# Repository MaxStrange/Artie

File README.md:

# Artie

**This code is pre-release: you cannot yet build an Artie bot nor can you use the framework - not all of the software and hardware is ready!**

Artie is an open source developmental robotics platform. This repository is the
documentation hub and the place to start; the software itself lives in the component
repositories listed below.

The purpose of Artie is twofold: data collection and testing developmental robotics theories.

The vision is that Artie will be fully open source, 3D-printable, and as cheap as is feasible,
while still being easy to use and extend.

Fundamentally, this project provides:

* A software development kit (ArDK) - code libraries for use building robots
* A platform - a suite of tools and documents for building a Kubernetes cluster designed from the ground-up
  for research
* A reference robot (Artie00) - if you want to build your own completely different robot from the one we
  use, that's fine! But you might want to use Artie00 as a reference

## The repositories

| Repository | What it is |
|---|---|
| **Artie** (this one) | Documentation, architecture, getting started. Cite this repository. |
| [ArDK](https://github.com/ArtieBots/ArDK) | The Artie Development Kit: the libraries you write applications and drivers against, the platform services, the base Docker image, and the protocol specifications. |
| [ArtieTool](https://github.com/ArtieBots/ArtieTool) | Builds, tests, flashes and deploys everything. Installs the `artie-tool` command. |
| [ArtieWorkbench](https://github.com/ArtieBots/ArtieWorkbench) | The graphical application most people use to set up and drive an Artie Framework robot. |
| [ArtieCLI](https://github.com/ArtieBots/ArtieCLI) | A command line interface to a running robot, for testing and low-level debugging. |
| [ArtieDaemons](https://github.com/ArtieBots/ArtieDaemons) | Host daemons for the Kubernetes cluster an Artie robot runs on. |
| [Artie00](https://github.com/ArtieBots/Artie00) | The first Artie: its hardware manifest, bill of materials, firmware, drivers and schematics. |

Your own code stays in your own repository. You depend on Artie's libraries, build your
applications and firmware into images following the usage guidelines, and deploy them
with Helm - normally through Artie Workbench or Artie Tool.

## Get Started

**Looking for the contributing guide?** [See here](./CONTRIBUTING.md)

### Using Artie

Most people will want Artie Workbench, which installs Artie Tool along with it. This is
a graphical application that should make using an Artie Framework robot easy (for a human):

```bash
pip install artieworkbench
artie-workbench
```

If you would rather work from a terminal, or you are automating something:

```bash
pip install artietool
artie-tool workspace status    # where each component resolves to
artie-tool workspace sync      # clone the components you want to build from source
artie-tool build all           # by default, builds the latest stable framework components
artie-tool deploy artie        # will only work if you have something to deploy to
```

Artie Tool reads its configuration from `~/.artie/config.yaml`, from `ARTIE_*` environment
variables, and from command line arguments, in increasing order of precedence. Point a
component at a checkout of your own and Artie Tool will build from it instead:

```yaml
# ~/.artie/config.yaml
workspace: ~/artie-workspace
repos:
  ardk: { path: ~/repos/ArDK }   # your working copy; sync leaves it alone; build will pick it up
```

Which versions of the components are tested against a real robot and therefore form a known stable
release is stated by a release manifest -
see [versioning and releases](./docs/contributing/versioning.md).
*That manifest is what to attach to an experiment's data and cite in a paper.*

### Building Artie00

Before you can use Artie, you need to build him.

**Please note:** you cannot yet build an Artie! These instructions will certainly change, the bill of materials
will change, the schematics will change, etc.

Building Artie is composed of the following steps:

1. Get your parts
1. Flash the parts
1. Build your bot

[See here for the full instructions](./docs/building/building-artie-main.md)

### Building a Custom Robot

Artie Framework doesn't just work with official Artie robots! Artie Framework provides tools for managing
an awful lot of complexity behind convenient tooling while bringing you things like:

* Data provenance
* Reliability
* Repeatability

- the types of things that are super important in scientific endeavors.

[See here for how to bring your own robot](./docs/building/bring-your-own.md)

### Artie Out of the Box

Once you have built an Artie (or brought your own robot),
[see here for instructions on using your Artie](./docs/out-of-the-box/getting-started.md).

## Motivation

### Why Developmental Robotics?

Developmental robotics is the study of human development by means of simulating it.
It is an important field of study for at least the following reasons:

1. Developmental robotics informs the study of human development. What better way to test a theory
   of how a human develops than to try to build a human?
1. Developmental robotics informs the study of artificial intelligence. AI can benefit from any advances
   in our understanding of human intelligence.
1. Developmental robotics informs the study of robotics. Building a robot always involves solving difficult
   engineering problems. Building a robot that can learn and adapt like a human is even more difficult,
   and any advances in this field will likely have applications in more traditional robotics or in soft robotics.

Here's a great excerpt from Wikipedia:

> As in human children, learning is expected to be cumulative and of progressively increasing complexity,
  and to result from self-exploration of the world in combination with social interaction.
  The typical methodological approach consists in starting from theories of human and animal development
  elaborated in fields such as developmental psychology, neuroscience, developmental and evolutionary biology,
  and linguistics, then to formalize and implement them in robots

### Embodiment

A central tenet of developmental robotics is that embodiment (agency) is necessary for intelligence.
Human intelligence stems from a need to manipulate the world and ourselves in response to the world.
It does not exist in a vacuum. Hence, it makes sense to embody an intelligent agent in a physical
(or at least virtual) world.

### Why a Robot?

If developmental robotics is the study of human development by means of simulating it, why
build an actual robot? Why not just simulate one in a physics simulator?

The answer is simple: humans aren't simulated - they exist in a messy, physical world. Any theory
of how a human develops must ultimately be put to the test in the same world with the same parameters.
In fact, when you try to go from a theory to a physical implementation, you always find that the theory
was underspecified: in implementing the theory, you have to make decisions about things that the theory
did not address. This process of implementation forces you to refine the theory and address gaps that
you did not know existed.

Nonetheless, there is a place for virtual simulation in developmental robotics, and Artie
will hopefully incorporate a simulator, since working with an actual robot is way less convenient
than working in a video game, but this simulator is a long way off for now. Get in touch if
you'd like to help build it!

One last thing about robots: embodiment is a two-way street. Though you can get by to an extent with
datasets that are impersonal and aggregated (as in the typical supervised learning paradigm of machine learning),
humans do not learn this way. Humans learn from interacting with their environment and by their environment
interacting with them. Parents speak directly to their children using infant-directed speech, based on
what their children are currently doing. Teenagers navigate social environments that are unique to their
particular group of friends. Young adults take elective classes at university that are interesting to them.
*An intelligent agent has an active, often causative relationship with the data from which it learns.*
Hence, you need to place the subject into an environment to truly study the development of natural intelligence.

Finally, robots are awesome!

### Why not Buy a Robot that Already Exists?

We found that we needed a robot that fulfilled the following criteria:

* Open Source - both hardware and software
* Affordable - we wanted to be able to build multiple copies of the robot without grant funding.
  We think this is key: robotics research is slowly coming to the masses of hobbyists, students,
  and citizen scientists, but developmental robotics research is still mostly confined to well-funded labs.
* Designed for Developmental Robotics - many existing robots are designed for other purposes,
  such as research in traditional robotics, human-robot interaction, or AI. These robots never
  take into account the specific needs of developmental robotics research, such as the physical constraints
  of a human infant, or the physiological requirements of various sensor components. Artie is designed
  from the ground up with developmental robotics in mind: we have compromised on biomimeticity only as far
  as is absolutely necessary to make the robot affordable and buildable.
* Modular and Extensible - we wanted a robot that could be easily modified, extended, and repaired.
  Research moves quickly, and we wanted a robot that could keep pace.
  We also wanted a robot that could be customized to fit the needs of different researchers
  and different experiments, which means that we aren't building a robot - we are building a robotics ecosystem.
* Professional grade - we wanted a robot that was reliable and fun to use. Every layer of Artie's
  software stack is designed to be robust, maintainable, and to follow engineering best practices,
  so that researchers can focus on their research, not on debugging the robot.
* Data provenance and reproducibility - we wanted a robot that could keep track of where its data came from, so that
  researchers can be sure that their experiments are reproducible and that their data is trustworthy.
  Artie uses containerization and orchestration to ensure that software environments are consistent
  across different deployments. Additionally, even the single board computers are running custom
  Linux images built using Yocto, so that the entire software stack is under control: if it worked once,
  it should work every time; you are running an experiment with Artie, not just getting him to work this one time.

Alternatives exist, but they don't meet these criteria. For example, there's:
  - [Poppy](https://www.generationrobots.com/en/312-poppy-humanoid-robot), which is about $10k USD,
    and while it's open source and extensible, it's not designed specifically for developmental robotics; it is
    not biomimetic at all.
  - [Nao](https://en.wikipedia.org/wiki/Nao_(robot)), which is about $15k USD, and while it is well-regarded
    and used extensively, its hardware is not extensible or modifiable, and it
    is designed more for human-robot interaction than developmental robotics. Again, very little biomimeticity.
  - [iCub](https://icub.iit.it/products/product-catalog), which is about $250k USD, and while it is
    designed for developmental robotics and has a high degree of biomimeticity, its cost
    makes it inaccessible to most researchers - particularly to citizen scientists or students.
  - [Berkeley Humanoid Lite](https://lite.berkeley-humanoid.org/), which is about $5k USD, and while it is affordable
    and open source, it is not designed specifically for developmental robotics, again with very little biomimeticity
    in mind.

### Why not ROS?

Additionally, we did not use ROS (Robot Operating System) as the basis for Artie's software stack.
While ROS is a great tool for traditional robotics development, we felt it was not well-suited
for reproducible developmental robotics research. ROS's architecture is not designed
for containerization and orchestration, which are key to ensuring that experiments
are reproducible and that software environments are consistent across different deployments.
Also, while ROS has a huge ecosystem and excellent community support/adoption, it is too general purpose
for our needs: we wanted a software stack that was specifically designed for developmental robotics and for research.
Really the only thing that we could have used from ROS was its inter-process communication (IPC) mechanisms.
I suppose its physics simulator would have been nice, too.

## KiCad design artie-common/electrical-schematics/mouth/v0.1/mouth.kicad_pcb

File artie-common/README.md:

# Artie Common

This folder contains a bunch of common components used between different versions of Artie,
but which do not belong in the framework (i.e., they do not necessarily belong to *all*
versions of Artie, but they are used by more than one).

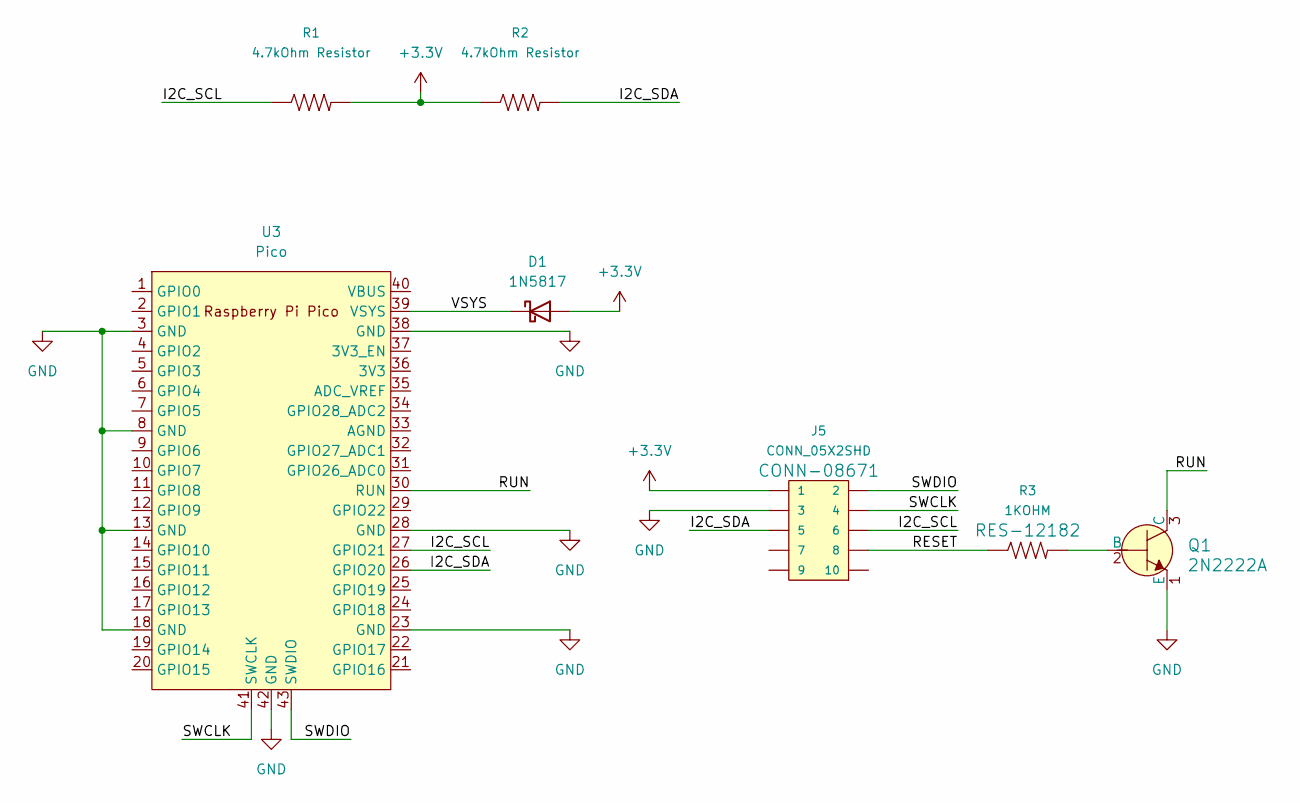
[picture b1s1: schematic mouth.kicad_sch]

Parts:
D1: 1N5817; D_DO-41_SOD81_P10.16mm_Horizontal
J5: CONN_05X2SHD; 2X5-SHROUDED
Q1: 2N2222A; TO-18-3; MPN 2N2222A; Digi-Key_PN 2N2222ACS-ND
R1, R2: 4.7kOhm Resistor; AXIAL-0.3
R3: 1KOHM; AXIAL-0.3-KIT
U3: Pico; RPi_Pico_SMD_TH

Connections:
+3.3V: D1.2 (A), J5.1, R1.P$2 (2), R2.P$1 (1)
/I2C_SCL: J5.6, R1.P$1 (1), U3.27 (GPIO21)
/I2C_SDA: J5.5, R2.P$2 (2), U3.26 (GPIO20)
/RESET: J5.8, R3.P$1 (1)
/RUN: Q1.3 (C), U3.30 (RUN)
/SWCLK: J5.4, U3.41 (SWCLK)
/SWDIO: J5.2, U3.43 (SWDIO)
/VSYS: D1.1 (K), U3.39 (VSYS)
GND: J5.3, Q1.1 (E), U3.3 (GND), U3.8 (GND), U3.13 (GND), U3.18 (GND), U3.23 (GND), U3.28 (GND), U3.38 (GND), U3.42 (GND)
unnamed: Q1.2 (B), R3.P$2 (2)

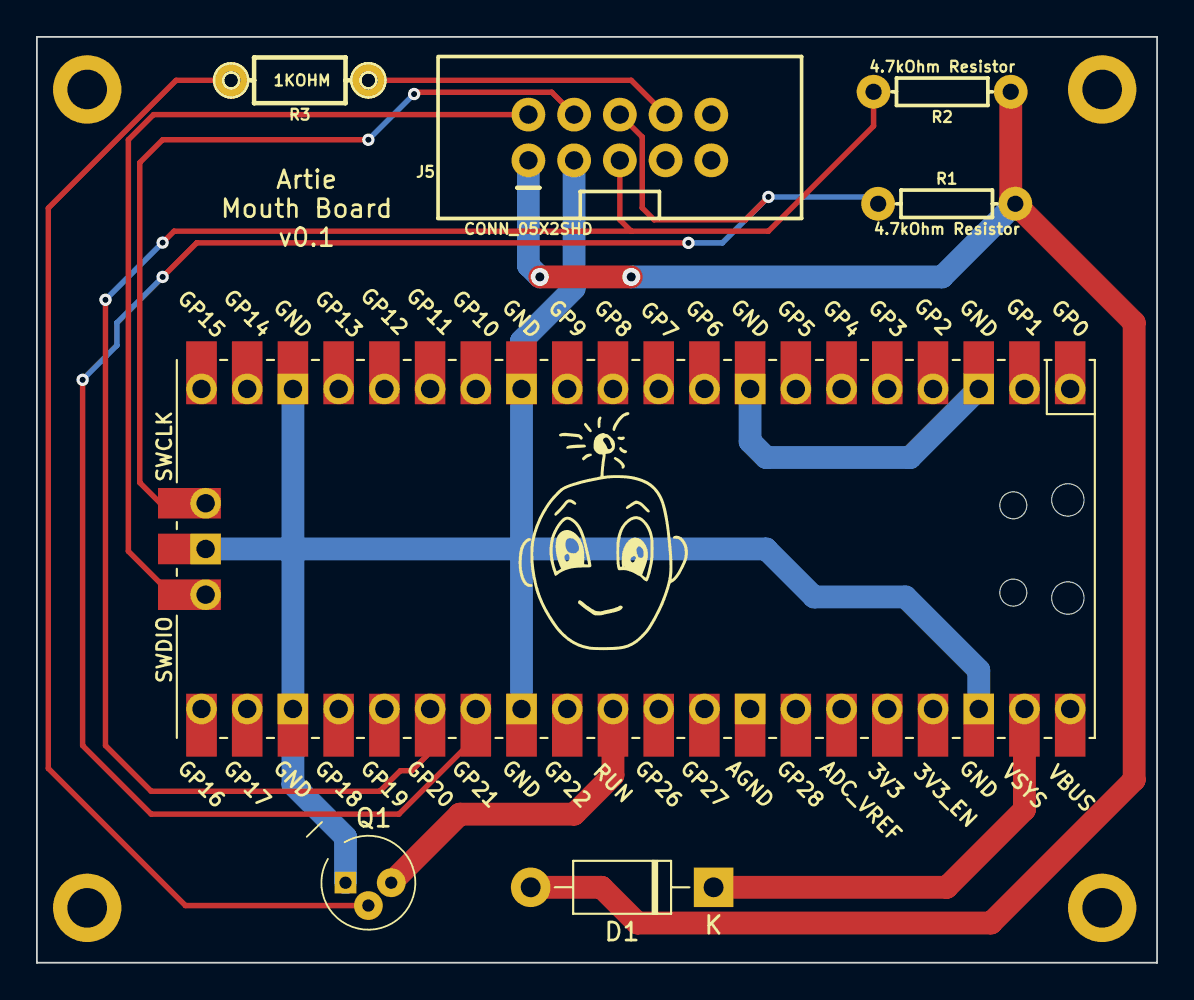
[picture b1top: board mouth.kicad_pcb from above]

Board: 2 copper layers, 62.2 x 51.4 mm, 7 parts (0 on the bottom side), 10 nets.

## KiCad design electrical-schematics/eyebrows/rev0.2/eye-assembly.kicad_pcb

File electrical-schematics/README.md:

# Electrical Schematics

This directory contains all the schematics for the various circuit boards you need to make to
build your very own Artie.

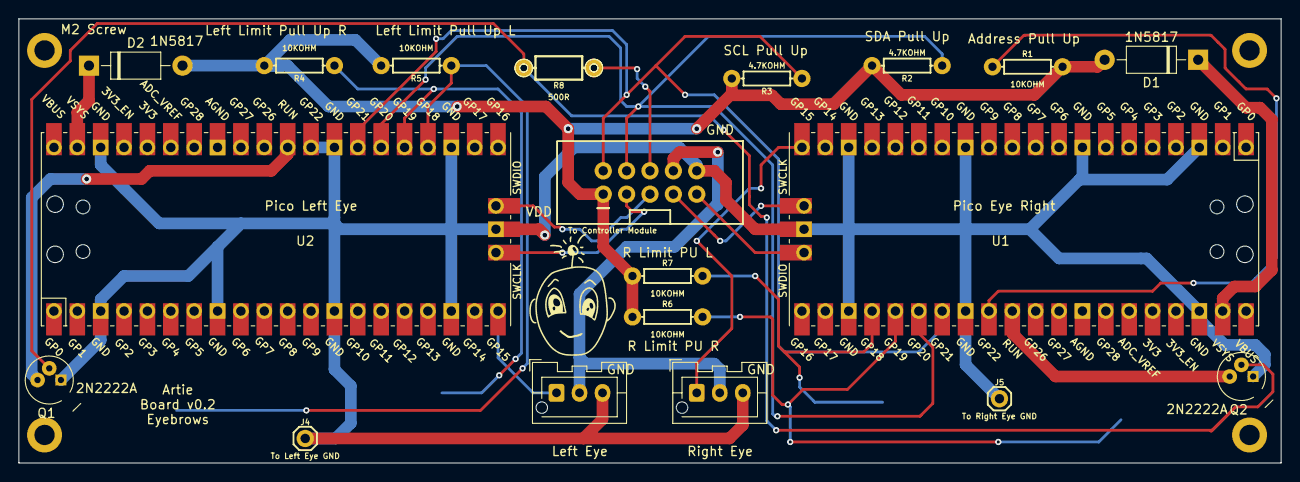
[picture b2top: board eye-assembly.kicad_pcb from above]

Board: 2 copper layers, 137.2 x 48.3 mm, 19 parts (0 on the bottom side), 22 nets.

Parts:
D1, D2: 1N5817; D_DO-41_SOD81_P10.16mm_Horizontal
J1: To Controller Module; 2X5-SHROUDED
J4: To Left Eye GND; 1X01
J5: To Right Eye GND; 1X01
M1, M2: SERVO; JST_XA_B03B-XASK-1-A_1x03_P2.50mm_Vertical
Q1, Q2: 2N2222A; TO-18-3
R1, R4, R5, R6, R7: 10KOHM; AXIAL-0.3
R2, R3: 4.7KOHM; AXIAL-0.3
R8: 500R; AXIAL-0.3-KIT
U1: Pico Eye Right; RPi_Pico_SMD_TH
U2: Pico Left Eye; RPi_Pico_SMD_TH

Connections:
3.3V: D1.2 (A), D2.2 (A), J1.1, R1.P$2 (2), R2.P$2 (2), R3.P$2 (2), R4.P$2 (2), R5.P$2 (2), R6.P$1 (1), R7.P$1 (1)
5V: J1.8, M1.2 (V+), M2.2 (V+)
/I2C_SCL: J1.2, R3.P$1 (1), U1.27 (GPIO21), U2.27 (GPIO21)
/I2C_SDA: J1.4, R2.P$1 (1), U1.26 (GPIO20), U2.26 (GPIO20)
/IRQ_LIMIT_L_U1: R7.P$2 (2), U1.24 (GPIO18)
/IRQ_LIMIT_L_U2: R5.P$1 (1), U2.24 (GPIO18)
/IRQ_LIMIT_R_U1: R6.P$2 (2), U1.25 (GPIO19)
/IRQ_LIMIT_R_U2: R4.P$1 (1), U2.25 (GPIO19)
/PWM_M1: M1.1 (SIG), U1.20 (GPIO15)
/PWM_M2: M2.1 (SIG), U2.20 (GPIO15)
/RESET: J1.6, R8.P$1 (1)
/RUN_LEFT: Q1.3 (C), U2.30 (RUN)
/RUN_RIGHT: Q2.3 (C), U1.30 (RUN)
/SWCLK_LEFT: J1.3, U2.41 (SWCLK)
/SWCLK_RIGHT: J1.7, U1.41 (SWCLK)
/SWDIO_LEFT: J1.5, U2.43 (SWDIO)
/SWDIO_RIGHT: J1.9, U1.43 (SWDIO)
/VSYS_L: D2.1 (K), U2.39 (VSYS)
/VSYS_R: D1.1 (K), U1.39 (VSYS)
GND: J1.10, J4.1, J5.1, M1.3 (GND), M2.3 (GND), Q1.1 (E), Q2.1 (E), U1.3 (GND), U1.8 (GND), U1.13 (GND), U1.18 (GND), U1.23 (GND), U1.28 (GND), U1.38 (GND), U1.42 (GND), U2.3 (GND), U2.8 (GND), U2.13 (GND), U2.18 (GND), U2.23 (GND), U2.28 (GND), U2.29 (GPIO22), U2.38 (GND), U2.42 (GND)
unnamed: Q1.2 (B), Q2.2 (B), R8.P$2 (2)
unnamed: R1.P$1 (1), U1.29 (GPIO22)

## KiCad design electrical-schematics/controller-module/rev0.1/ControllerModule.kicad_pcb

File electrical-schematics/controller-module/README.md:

# Controller Module Electrical Schematics

This folder contains the schematics for the circuit board that is housed in the controller module.

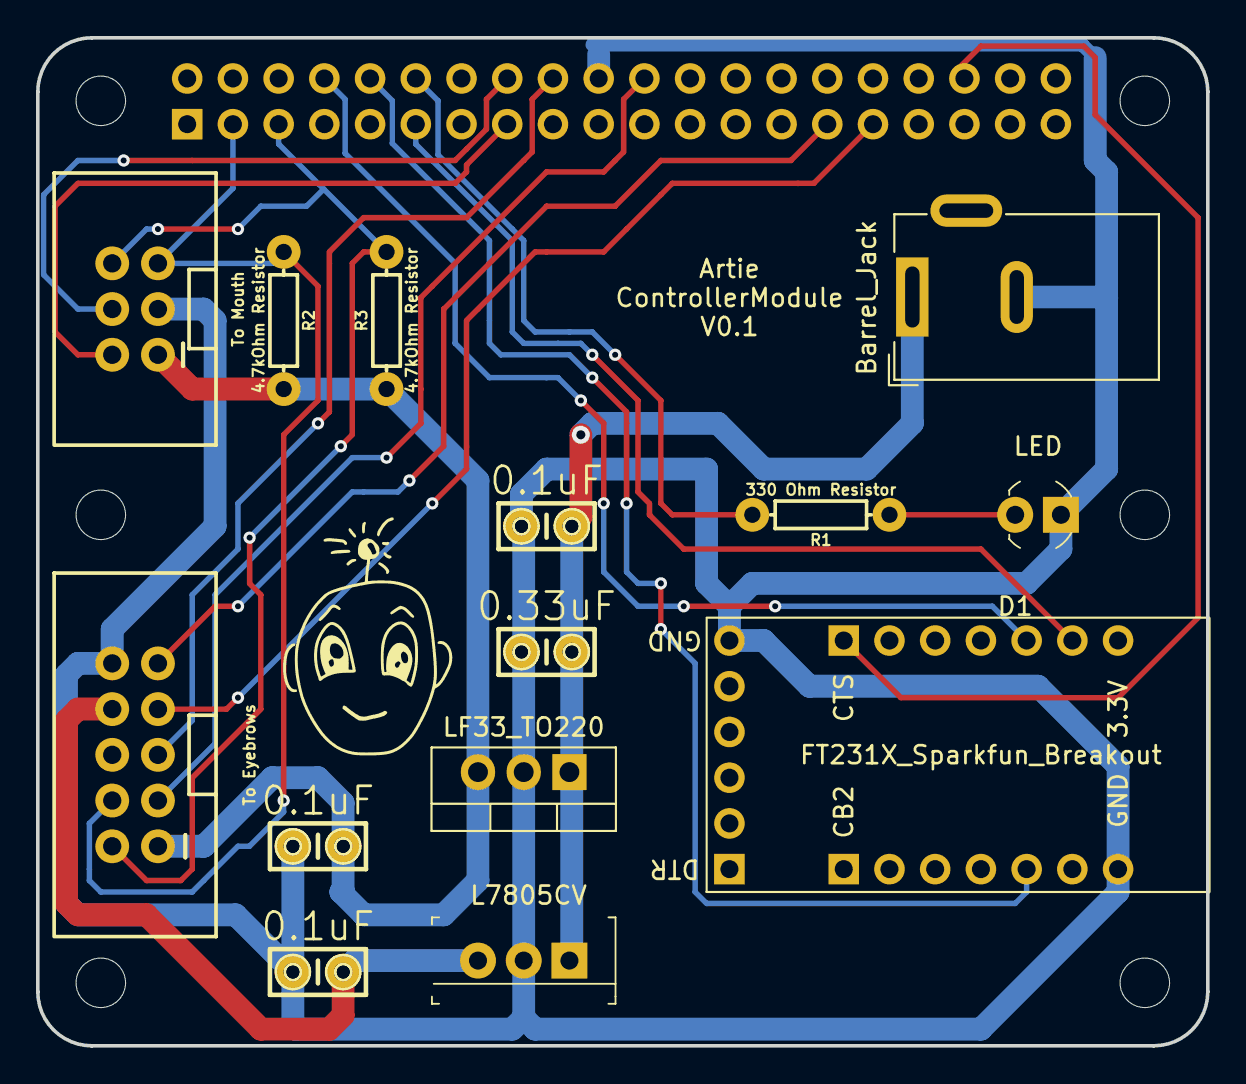
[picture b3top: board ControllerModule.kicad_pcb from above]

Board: 2 copper layers, 65.0 x 56.0 mm, 21 parts (1 on the bottom side), 18 nets.

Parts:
C1: 0.33uF; CAP-PTH-SMALL-KIT
C2, C3, C4: 0.1uF; CAP-PTH-SMALL-KIT
D1: LED; LED_3mm_Radial
H1, H2, H3, H4, H5, H6: MountingHole; MountingHole_2.75mm_NoPad
J1: Raspberry_Pi_B; PinSocket_2x20_P2.54mm_Vertical
J2: FT231X_Sparkfun_Breakout
J3: Barrel_Jack; BarrelJack_Wuerth_6941xx301002
J4: To Eyebrows; 2X5-SHROUDED
J5: To Mouth; 2X3-SHROUDED
R1: 330 Ohm Resistor; AXIAL-0.3
R2, R3: 4.7kOhm Resistor; AXIAL-0.3
U1: L7805CV; TO-220-3
U2: LF33_TO220; TO-220-3_Vertical

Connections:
3.3V: C4.1, J4.1, J5.1, R2.P$2 (2), R3.P$1 (1), U2.3 (VO)
5V: C3.1, J4.8, U1.3 (OUT)
+9V: C1.1, C2.1, J3.1, U1.1 (IN), U2.1 (VI)
/CTS: J1.36 (GPIO16), J2.7 (CTS)
/I2C_SCL: J1.5 (SCL/GPIO3), J4.2, J5.6, R3.P$2 (2)
/I2C_SDA: J1.3 (SDA/GPIO2), J4.4, J5.5, R2.P$1 (1)
/LED: J1.12 (GPIO18/PWM0), R1.P$2 (2)
/RTS: J1.11 (GPIO17), J2.12 (RTS)
/SWCLK_EYEBROW_L: J1.22 (GPIO25), J4.3
/SWCLK_EYEBROW_R: J1.31 (GCLK2/GPIO6), J4.7
/SWCLK_MOUTH: J1.16 (GPIO23), J5.4
/SWDIO_EYEBROW_L: J1.18 (GPIO24), J4.5
/SWDIO_EYEBROW_R: J1.29 (GCLK1/GPIO5), J4.9
/SWDIO_MOUTH: J1.15 (GPIO22), J5.2
/UART_RX: J1.10 (GPIO15/RXD), J2.16 (TX)
/UART_TX: J1.8 (GPIO14/TXD), J2.11 (RX)
GND: C1.2, C2.2, C3.2, C4.2, D1.1 (K), J1.20 (GND), J2.6 (GND), J2.14 (GND), J3.2, J4.10, J5.3, U1.2 (GND), U2.2 (GND)
unnamed: D1.2 (A), R1.P$1 (1)

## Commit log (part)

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2020-11-23 WIP: datasets
2022-12-08 Add docs and FW for eyebrows
2022-12-08 Eyebrows: update FW to use 2 boards
2023-02-22 Prepare cli for yocto consumption
2023-02-24 Update cli sudo access
2023-02-24 Fix getuser
2023-02-24 Update sudo
2023-03-13 Add libraries and eyebrow user space driver
2023-03-13 Update Python build scripts
2023-03-13 Fix import error in artiecli
2023-03-13 Fixes
2023-03-14 Add LED daemon for controller-node
2023-03-15 Fix some bugs
2023-03-15 Fix path to Python3
2023-03-15 Migrate from dbus to sockets in led daemon
2023-03-16 Remove debug labeling in LCD
2023-03-17 Add MCU reset feature
2023-03-17 Fix FW subsystem in cli
2023-03-17 Update everything to use a single board config file
2023-03-17 Fix swd config population script
2023-03-19 Squashed a few commits
    Controller Module PCB
    BME sensor
    Eyebrows compiling
    Mouth driver and CLI
    Mouth FW
2023-03-19 Mouth
2023-03-27 Fix Dockerfile
2023-03-27 Build system
2023-04-05 Complete mouth FW and write some docs
2023-04-19 Schematics and BOM Updates
2023-04-19 Fix CLI to use 'set-defaults'
2023-04-21 Build tool
2023-04-21 CAN Bus Protocol Specifications
2023-07-11 Refactor Artie Tool
    Also a bunch of other stuff :D
2023-07-12 Add GitHub Actions
2023-07-14 Add GitHub Actions CI
2023-10-26 Dev work and docs
2023-10-26 Update tests in pipeline
2023-10-27 Attempt to fix compose json bug
2023-10-27 Fix for the fix
2023-10-27 Update a doc
2023-10-27 Update CLI for use on control node
2023-10-27 Minor fix
2023-10-27 Fixup
2023-10-31 WIP: Release Process
2023-10-31 Update chart
2023-10-31 Add release workflow
2023-10-31 Multi arch images and tests
2023-10-31 Update to include arch tags
2023-10-31 Update values
2023-10-31 Add docker manifest (multi-arch) images
2023-11-01 Fix a couple of transient errors
2023-12-24 Add HW tests in artie tool, part 1
2023-12-24 First draft of HW tests
2023-12-24 Fix broken tests
2023-12-24 Deploying successfully
2023-12-24 Fix artie-name arg bug
2023-12-24 Fix some refactor bugs
2023-12-24 Update YAML for HW tests
2023-12-24 Update some readmes
2023-12-24 WIP: API for self test and status
2023-12-24 WIP: Fixing HW tests
2023-12-24 WIP: HW Testing
2023-12-24 WIP: Fixes for HW Tests
2023-12-24 Hardware tests failing properly
2023-12-24 WIP: HW Tests
2023-12-28 WIP: Refactor FW
2024-01-15 Refactor FW a bit
2025-11-20 WIP: Reset
2025-11-26 Move folders around
2025-11-26 WIP: Workbench
2025-11-30 WIP: Pipeline
2025-12-03 Remove OpenOCD dependencies
2025-12-06 WIP: Workbench GUI
2025-12-11 Updates to deployment
2025-12-11 Update installation procedure
2025-12-11 WIP: Installation
2025-12-13 WIP: Workbench and CLI refactor
2025-12-15 WIP: Workbench: Tests passing again
2025-12-16 WIP: Workbench: Logging and metrics API
2025-12-17 WIP: More workbench refactors and metrics stuff
2025-12-17 WIP: Building
2025-12-20 WIP: Updates to include Yocto
2025-12-20 WIP: Yocto build task
2025-12-20 WIP: Yocto
2025-12-23 Development documentation
2025-12-23 Circle CI
2025-12-23 Yocto building
2025-12-23 Updates to Yocto Build Job
2025-12-23 Update Yocto build task with CLI args for hosts and insecure repos
2025-12-23 Updates for Yocto
2025-12-23 Flash Yocto Image Job
2025-12-24 Deal with Python packaging crap
2025-12-24 Update requirements in cli
2025-12-24 WIP: Installation Procedure
2025-12-25 WIP: Installation Wizard
2025-12-25 WIP: Install
2025-12-26 WIP: Wizard
2025-12-26 Remove spurious colors.py
